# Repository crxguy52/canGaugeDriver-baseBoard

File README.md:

Hardware to to use [CANBed FD](https://www.seeedstudio.com/CANBed-FD-Arduino-CAN-FD-Development-Kit-p-4724.html) to read CAN data and drive gauges on a NB Miata

Used in conjunction with the [software](https://github.com/crxguy52/canGaugeDriver)

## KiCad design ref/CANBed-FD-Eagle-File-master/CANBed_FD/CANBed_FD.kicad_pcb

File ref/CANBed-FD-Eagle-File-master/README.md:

# CANBed-FD-Eagle-File
EAGLE FILE FOR CANBED-FD

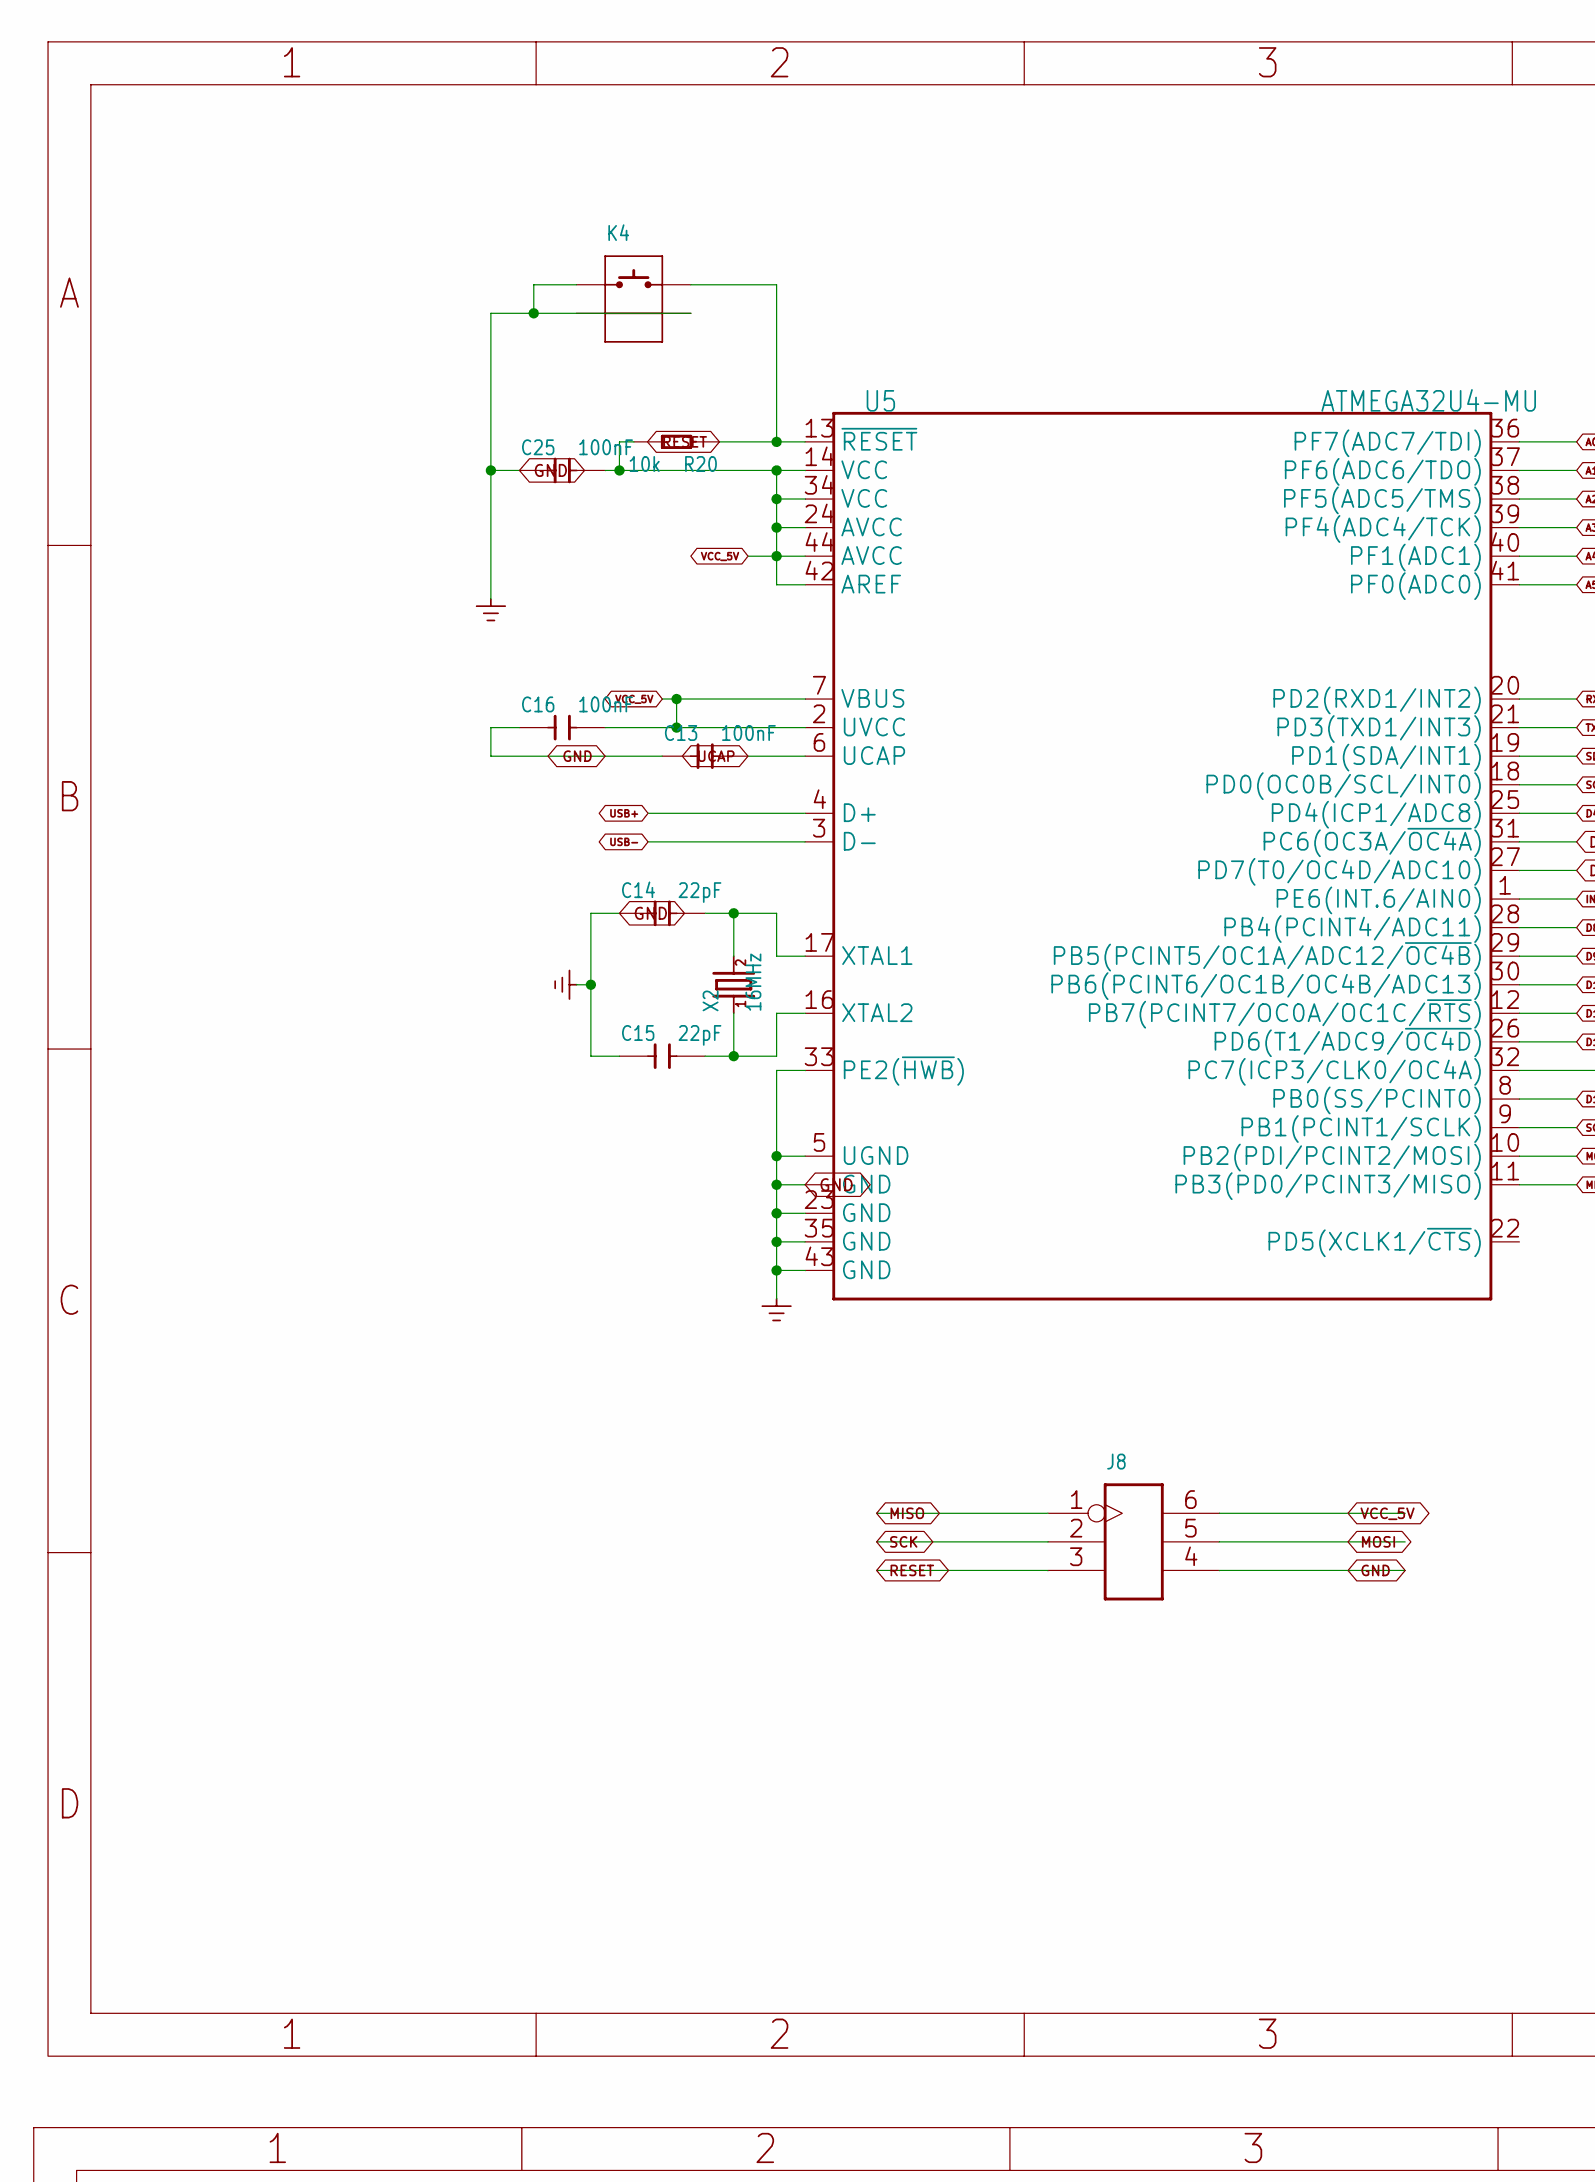
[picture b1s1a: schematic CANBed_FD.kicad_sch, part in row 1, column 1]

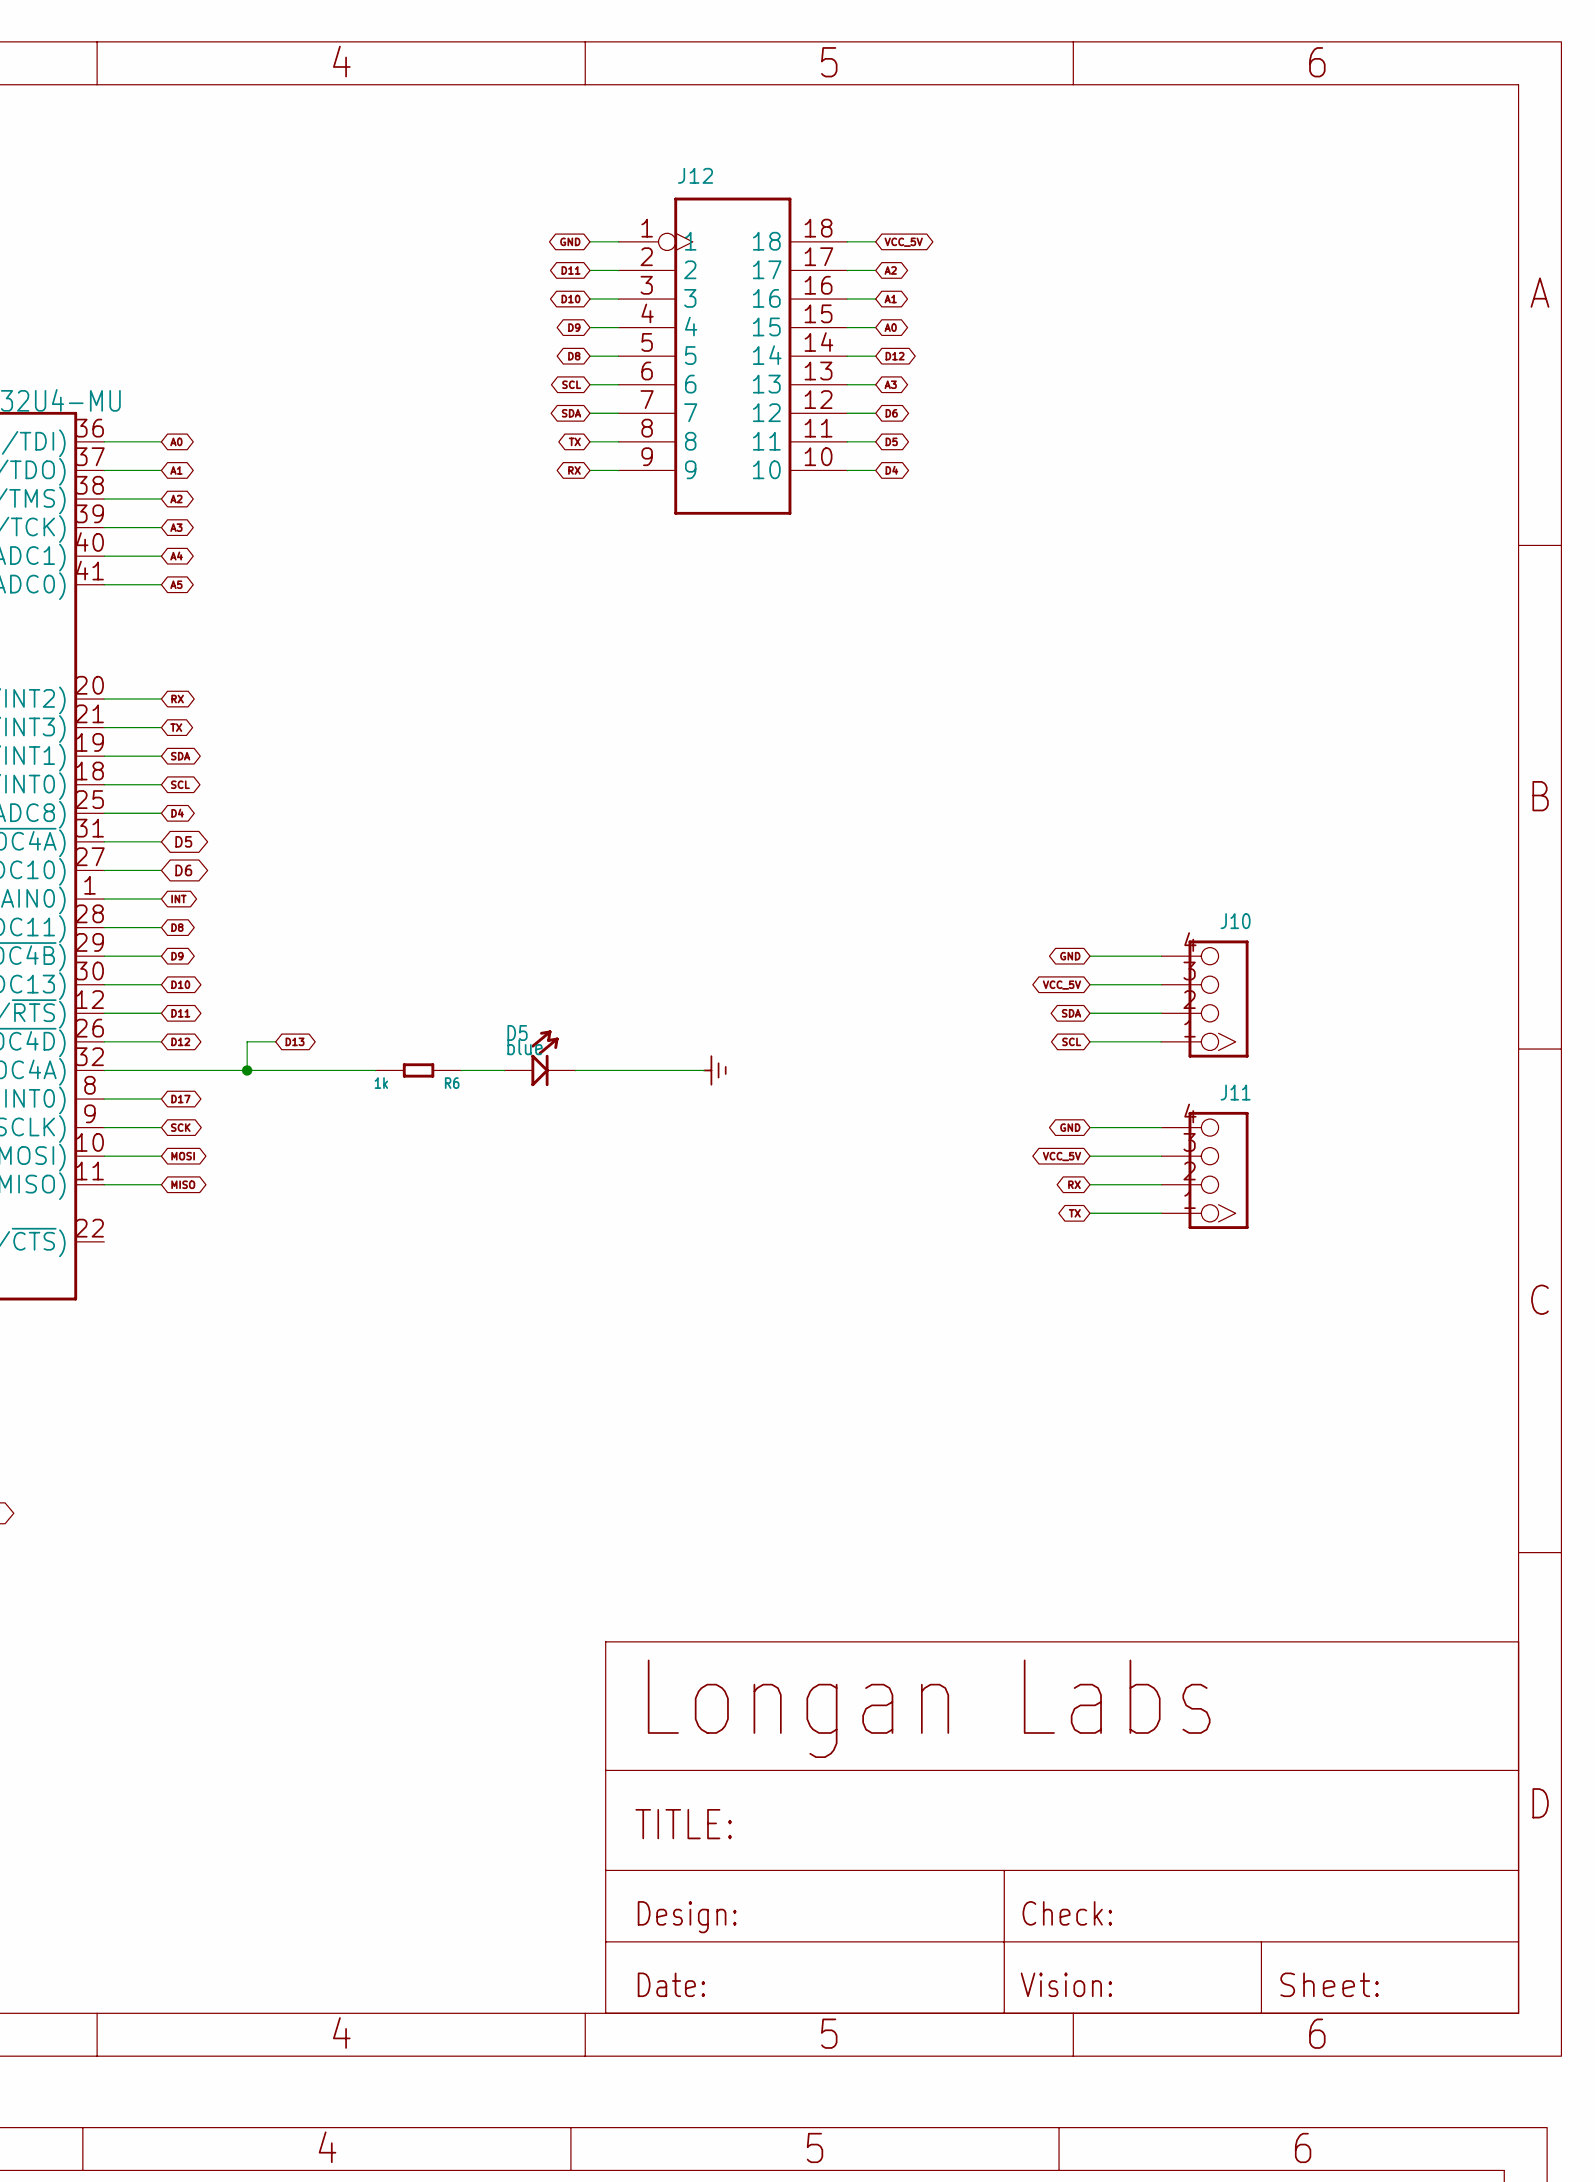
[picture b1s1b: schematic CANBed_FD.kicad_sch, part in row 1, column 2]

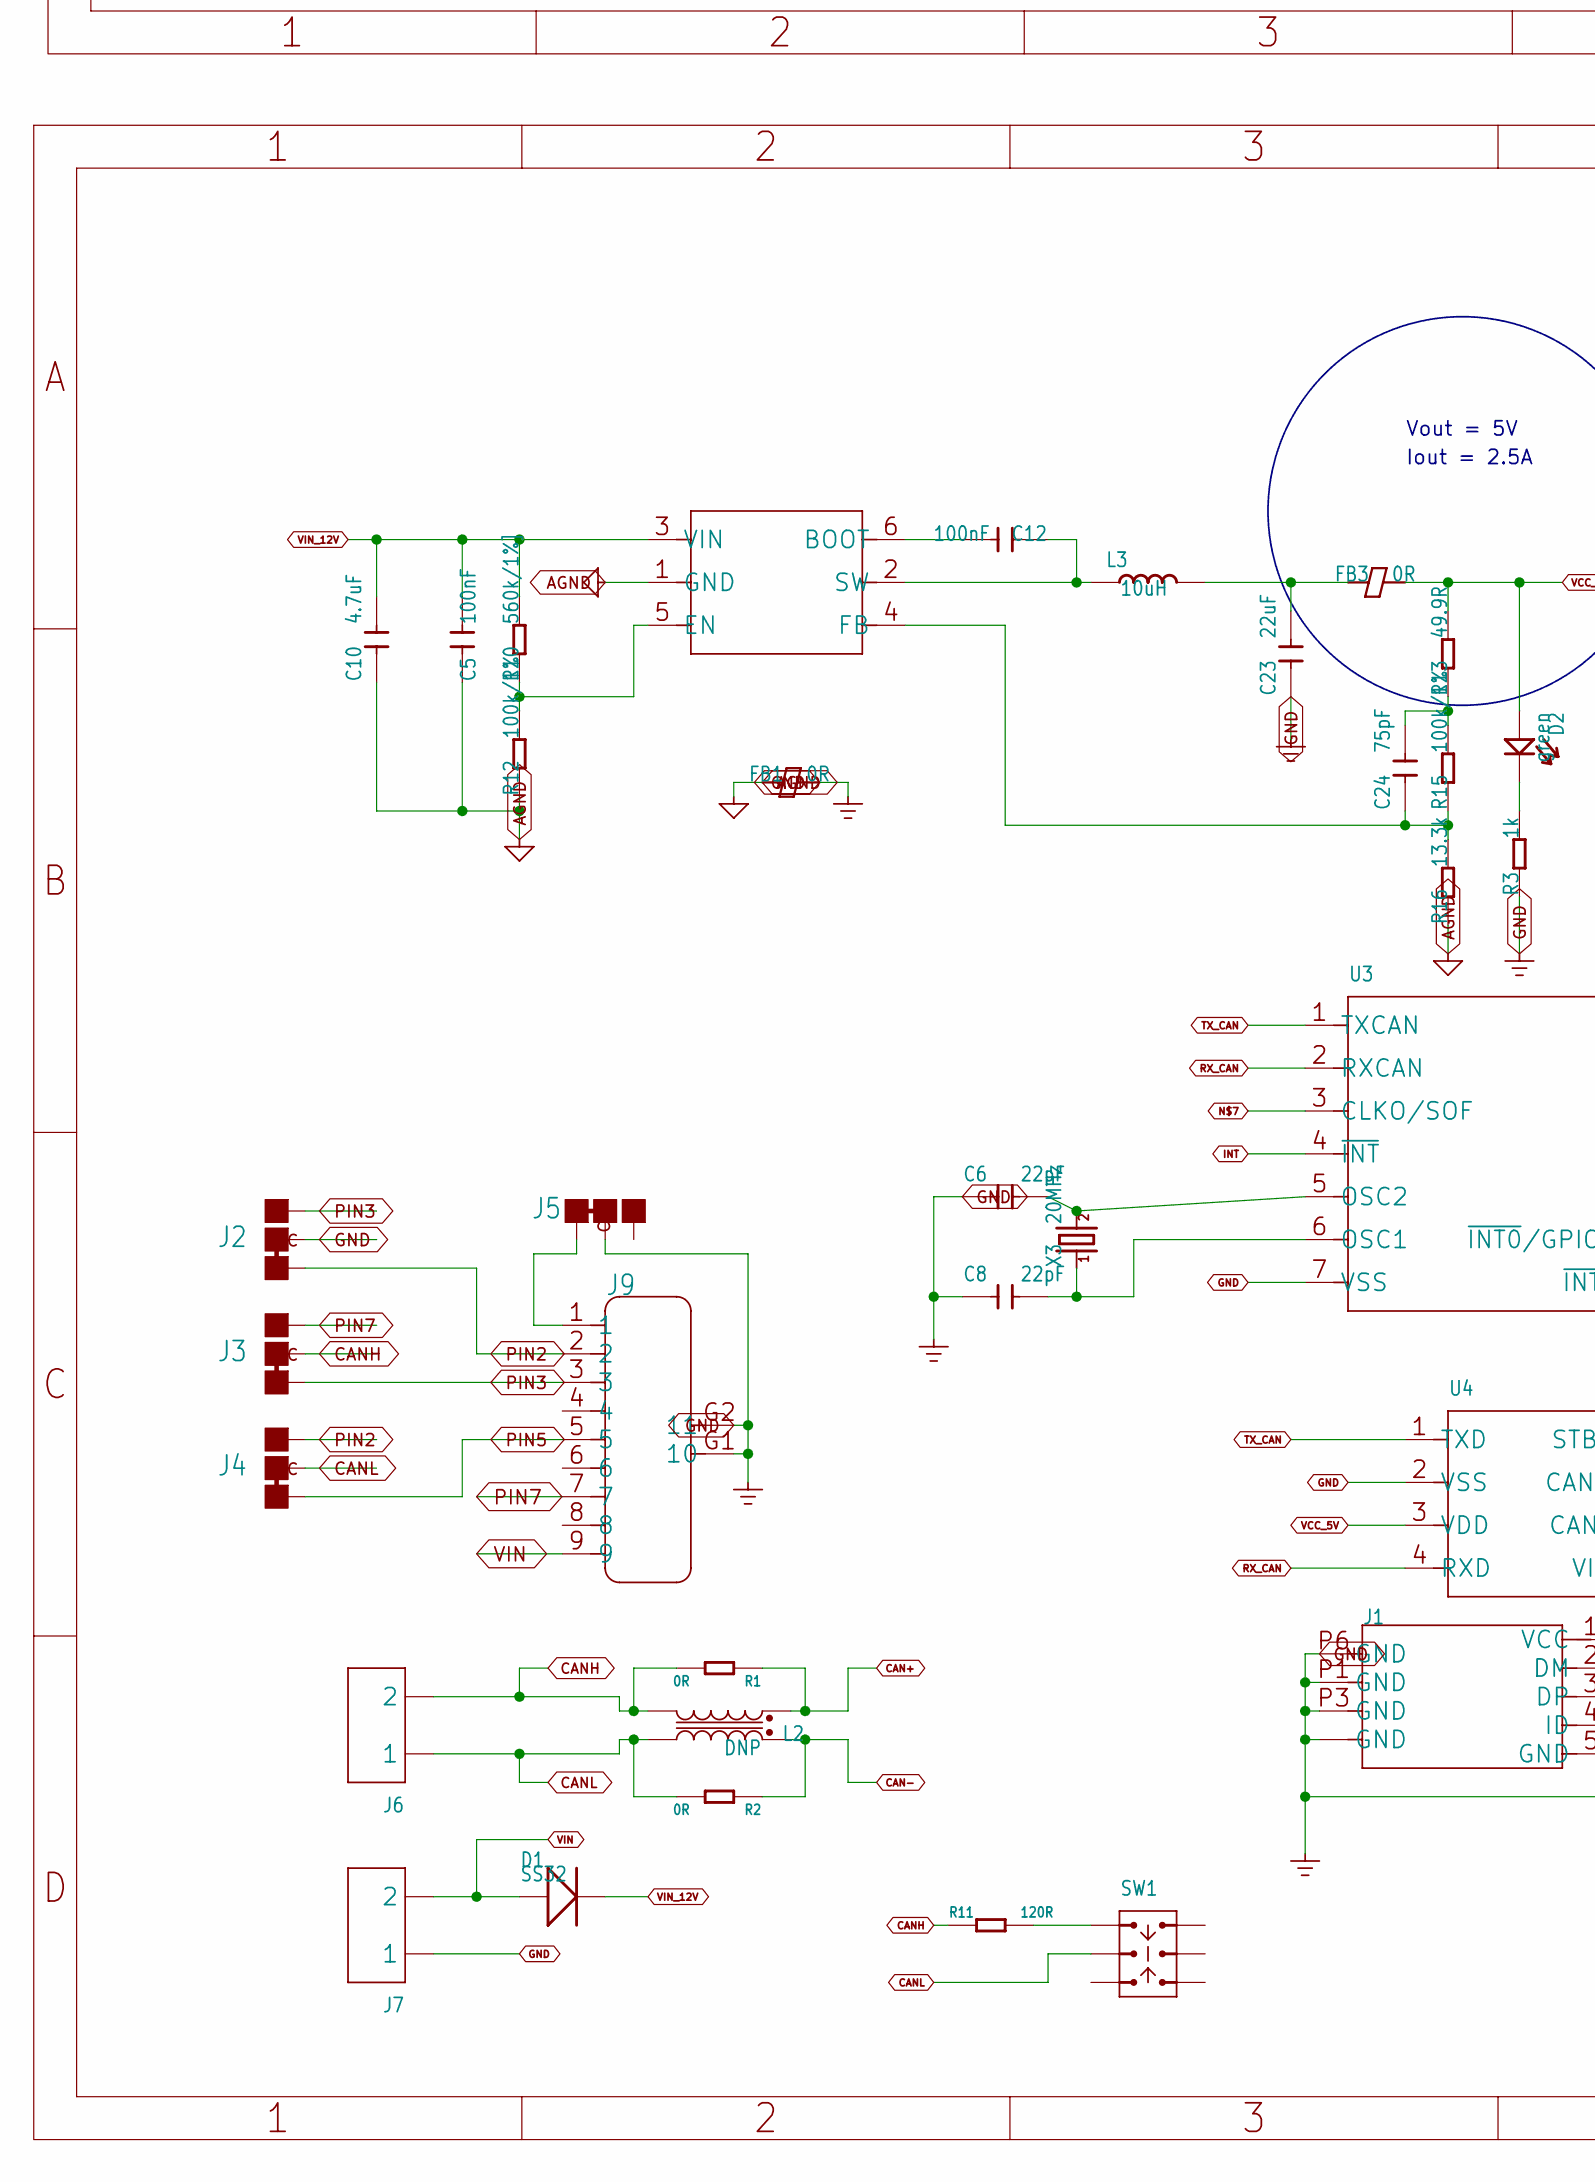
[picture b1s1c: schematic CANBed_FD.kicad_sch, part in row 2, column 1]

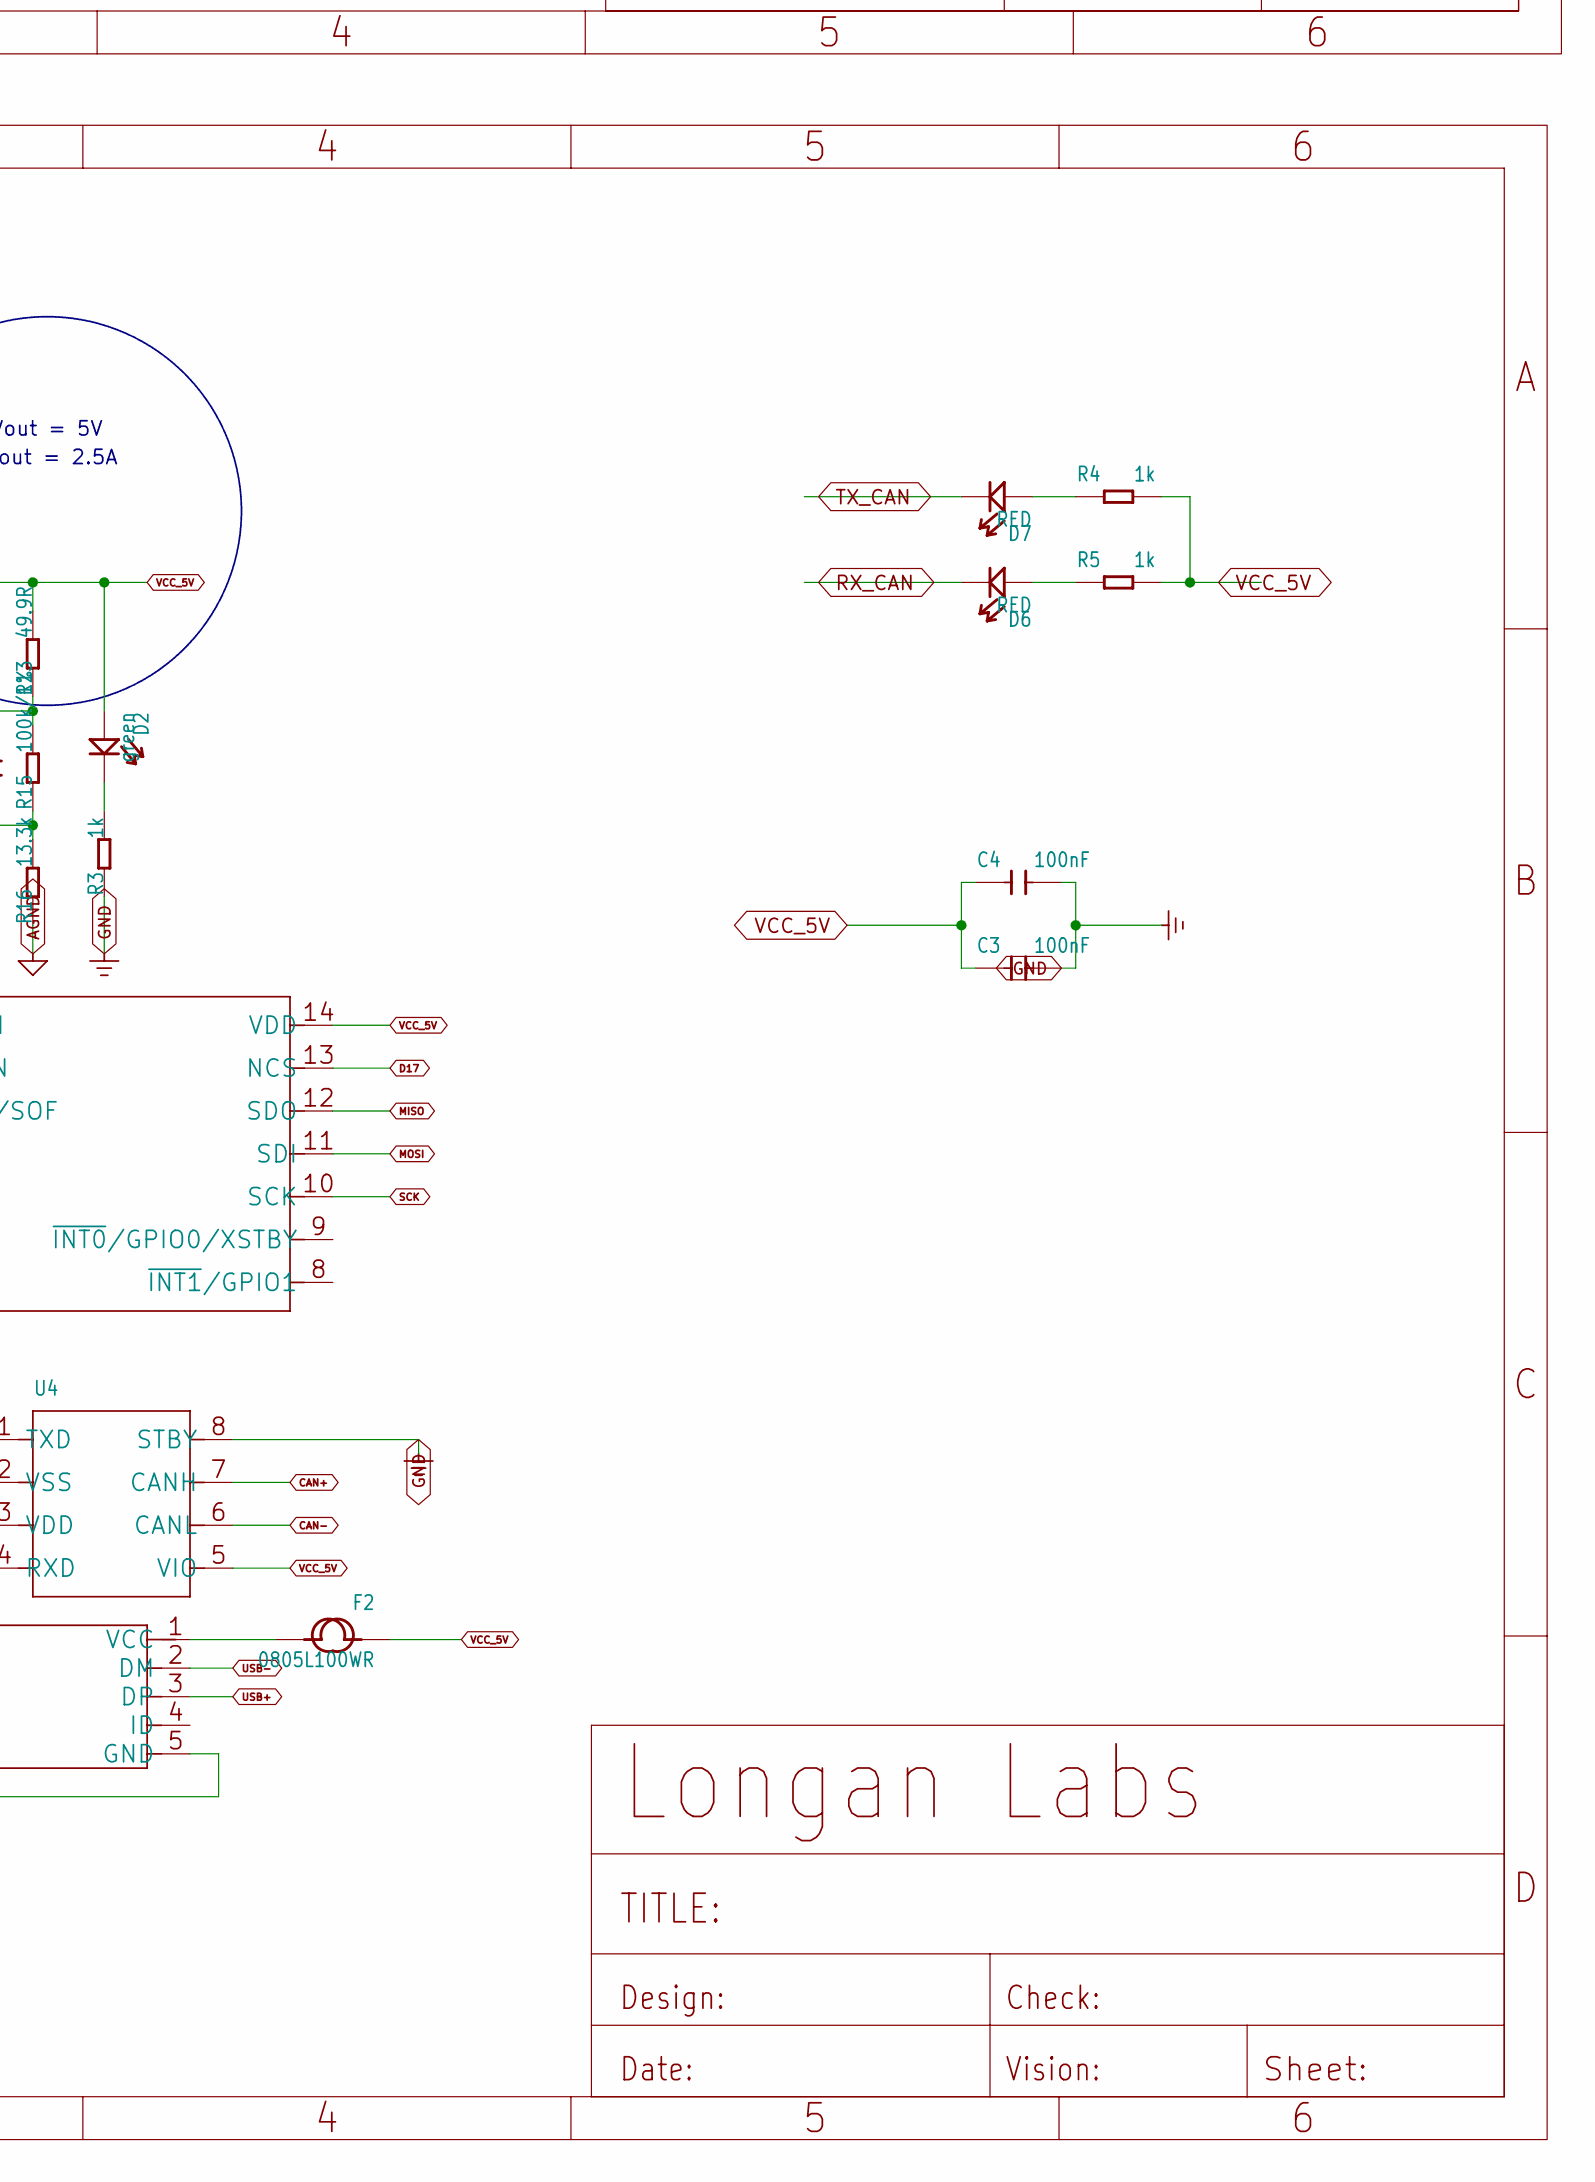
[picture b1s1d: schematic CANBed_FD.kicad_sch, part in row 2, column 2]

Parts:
C3, C4, C5, C12, C13, C16, C25: 100nF; C0603
C6, C8, C14, C15: 22pF; C0603
C10: 4.7uF; C1206
C23: 22uF; C1206
C24: 75pF; C0603
D1: SS32; DO-214AC
D2: green; LED-0603
D5: blue; LED-0603
D6, D7: RED; LED-0603
F2: 0805L100WR; F0805
FB1, FB3: 0R; F0805
J1: MICRO-USB5+4P-320010050; MICRO-USB5+5P-SMD-0.65-7.2X5.06MM
J2, J3, J4, J5: JUMPER-3P-SHORT; 3P-SMD-SHORT
J6, J7: SCREW-TERMINAL-2P'5.08'; H2-5.0-10.5X8.0MM
J8: HEADER-2X3P-2.54; H2X3-2.54
J9: DB9'MEAL'; DB9-MEAL
J10, J11: 320110033; HW4-2.0
J12: HEADER-2X9P-2.54; H2X9-2.54
K4: BUTTON-2+2P; SW2+2P-7.7X2.75X3.95MM
L2: DNP; INT4-0.85-2X1.25X1.2MM
L3: 10uH; INT2-SMD-6.6X7.1X3MM
R1, R2: 0R; R0603
R3, R4, R5, R6: 1k; R0603
R10: 560k/1%]; R0603
R11: 120R; R0603
R12, R15: 100k/1%; R0603
R13: 49.9R; R0603
R16: 13.3k; R0603
R20: 10k; R0603
SW1: SWITCH-2CH-6P-311010004; SW6-2.54-9.0X3.5X3.2+2.0MM
U3: CONTROLLER-MCP2517FD; SOIC14-1.27-8.6X3.9MM
U4: TRANSCEIVER-MCP2542; SOIC8-1.27-5X4MM
U5: ATMEGA32U4-MU; QFN44
U$11: PMIC-TPS54302; SOT-23-6
X2: 16MHz; HC49US
X3: 20MHz; HC49US

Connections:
A0: J12.15, U5.36 (PF7(ADC7/TDI))
A1: J12.16, U5.37 (PF6(ADC6/TDO))
A2: J12.17, U5.38 (PF5(ADC5/TMS))
A3: J12.13, U5.39 (PF4(ADC4/TCK))
A4: U5.40 (PF1(ADC1))
A5: U5.41 (PF0(ADC0))
AGND: C5.1, C10.1, FB1.1, R12.1, R16.1, U$11.1 (GND)
CAN+: L2.4, R1.1, U4.7 (CANH)
CAN-: L2.1, R2.1, U4.6 (CANL)
CANH: J3.MM (C), J6.2, L2.3, R1.2, R11.1
CANL: J4.MM (C), J6.1, L2.2, R2.2, SW1.COM1
D4: J12.10, U5.25 (PD4(ICP1/ADC8))
D5: J12.11, U5.31 (PC6(OC3A/~OC4A))
D6: J12.12, U5.27 (PD7(T0/OC4D/ADC10))
D8: J12.5, U5.28 (PB4(PCINT4/ADC11))
D9: J12.4, U5.29 (PB5(PCINT5/OC1A/ADC12/~OC4B))
D10: J12.3, U5.30 (PB6(PCINT6/OC1B/OC4B/ADC13))
D11: J12.2, U5.12 (PB7(PCINT7/OC0A/OC1C/~RTS))
D12: J12.14, U5.26 (PD6(T1/ADC9/~OC4D))
D13: R6.2, U5.32 (PC7(ICP3/CLK0/OC4A))
D17: U3.13 (NCS), U5.8 (PB0(SS/PCINT0))
EXT_PWR: F2.2, J1.1 (VCC)
GND: C3.2, C4.2, C6.1, C8.1, C13.1, C14.1, C15.1, C16.1, C23.1, C25.1, D5.-, FB1.2, J1.5 (GND), J1.P1 (GND), J1.P3 (GND), J1.P4 (GND), J1.P5 (GND), J1.P6 (GND), J2.MM (C), J5.MM (C), J7.1, J8.4, J9.G1 (10), J9.G2 (11), J10.4, J11.4, J12.1, K4.1, K4.S1, K4.S2, R3.1, U3.7 (VSS), U4.2 (VSS), U4.8 (STBY), U5.5 (UGND), U5.15 (GND), U5.23 (GND), U5.33 (PE2(~HWB)), U5.35 (GND), U5.43 (GND), U5.TAB (GND)
INT: U3.4 (~INT), U5.1 (PE6(INT.6/AIN0))
MISO: J8.1, U3.12 (SDO), U5.11 (PB3(PD0/PCINT3/MISO))
MOSI: J8.5, U3.11 (SDI), U5.10 (PB2(PDI/PCINT2/MOSI))
unnamed: D2.-, R3.2
unnamed: D7.+, R4.1
unnamed: R10.1, R12.2, U$11.5 (EN)
unnamed: C14.2, U5.17 (XTAL1), X2.2
unnamed: D5.+, R6.1
unnamed: C6.2, U3.5 (OSC2), X3.2
unnamed: C12.1, L3.1, U$11.2 (SW)
unnamed: C15.2, U5.16 (XTAL2), X2.1
unnamed: J5.11 (L), J9.1
unnamed: C12.2, U$11.6 (BOOT)
unnamed: D6.+, R5.1
unnamed: R11.2, SW1.CH1A
unnamed: C8.2, U3.6 (OSC1), X3.1
unnamed: C23.2, FB3.1, L3.2
unnamed: C24.2, R13.1, R15.2
unnamed: C24.1, R15.1, R16.2, U$11.4 (FB)
PIN2: J2.11 (L), J4.00 (R), J9.2
PIN3: J2.00 (R), J3.11 (L), J9.3
PIN5: J4.11 (L), J9.5
PIN7: J3.00 (R), J9.7
RESET: J8.3, K4.2, R20.1, U5.13 (~RESET)
RX: J11.2, J12.9, U5.20 (PD2(RXD1/INT2))
RX_CAN: D6.-, U3.2 (RXCAN), U4.4 (RXD)
SCK: J8.2, U3.10 (SCK), U5.9 (PB1(PCINT1/SCLK))
SCL: J10.1, J12.6, U5.18 (PD0(OC0B/SCL/INT0))
SDA: J10.2, J12.7, U5.19 (PD1(SDA/INT1))
TX: J11.1, J12.8, U5.21 (PD3(TXD1/INT3))
TX_CAN: D7.-, U3.1 (TXCAN), U4.1 (TXD)
UCAP: C13.2, U5.6 (UCAP)
USB+: J1.3 (DP), U5.4 (D+)
USB-: J1.2 (DM), U5.3 (D-)
VCC_5V: C3.1, C4.1, C16.2, C25.2, D2.+, F2.1, FB3.2, J8.6, J10.3, J11.3, J12.18, R4.2, R5.2, R13.2, R20.2, U3.14 (VDD), U4.3 (VDD), U4.5 (VIO), U5.2 (UVCC), U5.7 (VBUS), U5.14 (VCC), U5.24 (AVCC), U5.34 (VCC), U5.42 (AREF), U5.44 (AVCC)
VIN: D1.1 (+), J7.2, J9.9
VIN_12V: C5.2, C10.2, D1.2 (-), R10.2, U$11.3 (VIN)

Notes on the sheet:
Iout = 2.5A
Vout = 5V

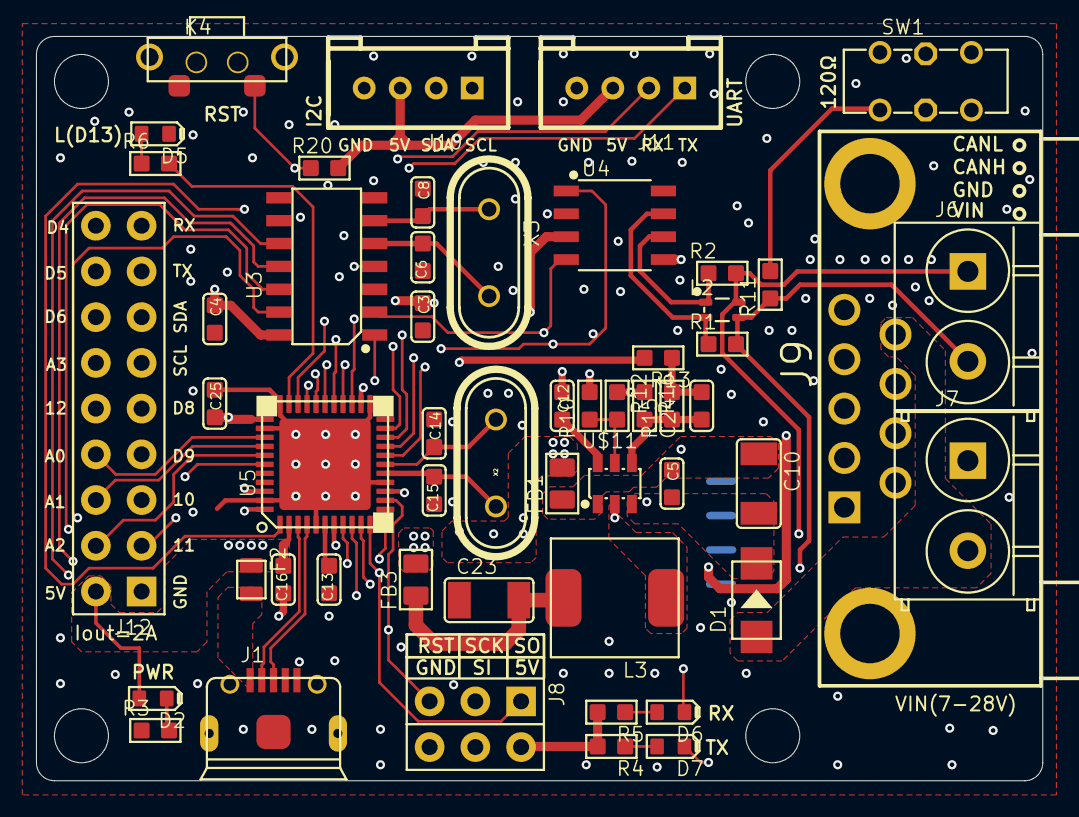
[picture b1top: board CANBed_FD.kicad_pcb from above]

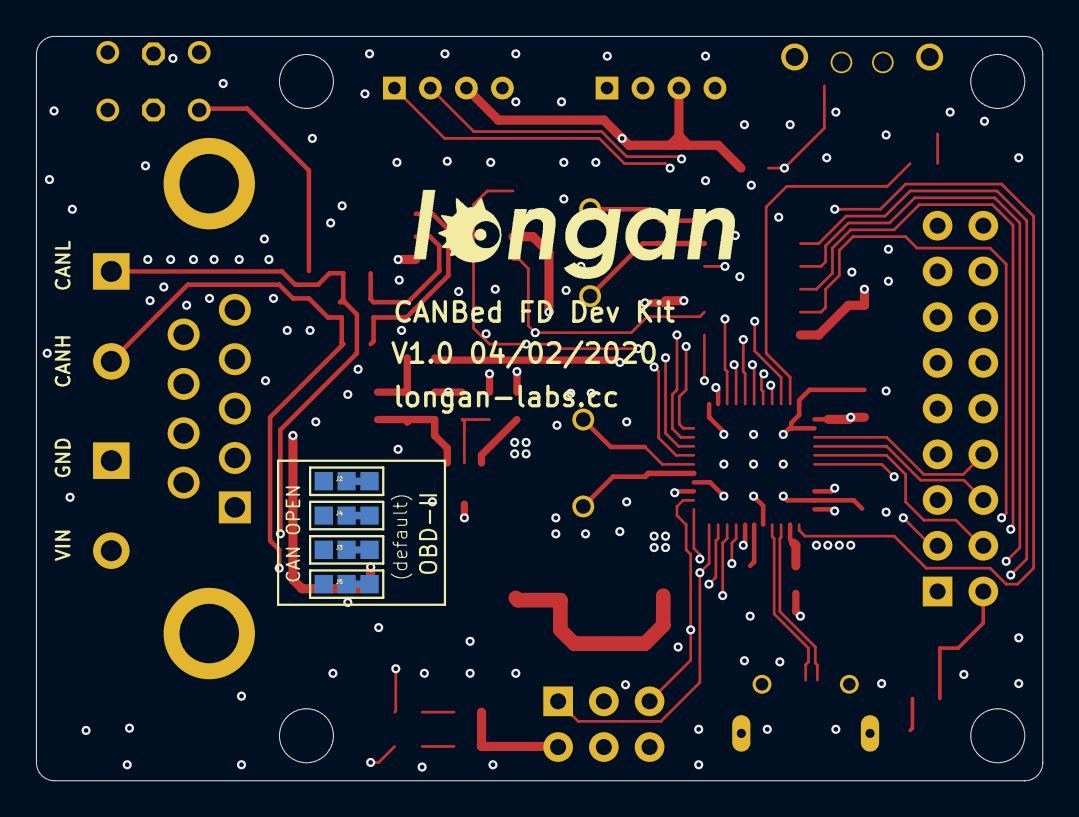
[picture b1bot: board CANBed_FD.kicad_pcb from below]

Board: 6 copper layers, 55.9 x 41.4 mm, 62 parts (5 on the bottom side), 58 nets.

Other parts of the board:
U$12: LONGAN-SILK-SMALL
UNK_HOLE_0: dummyfp0
UNK_HOLE_1: dummyfp1
UNK_HOLE_2: dummyfp2
UNK_HOLE_3: dummyfp3

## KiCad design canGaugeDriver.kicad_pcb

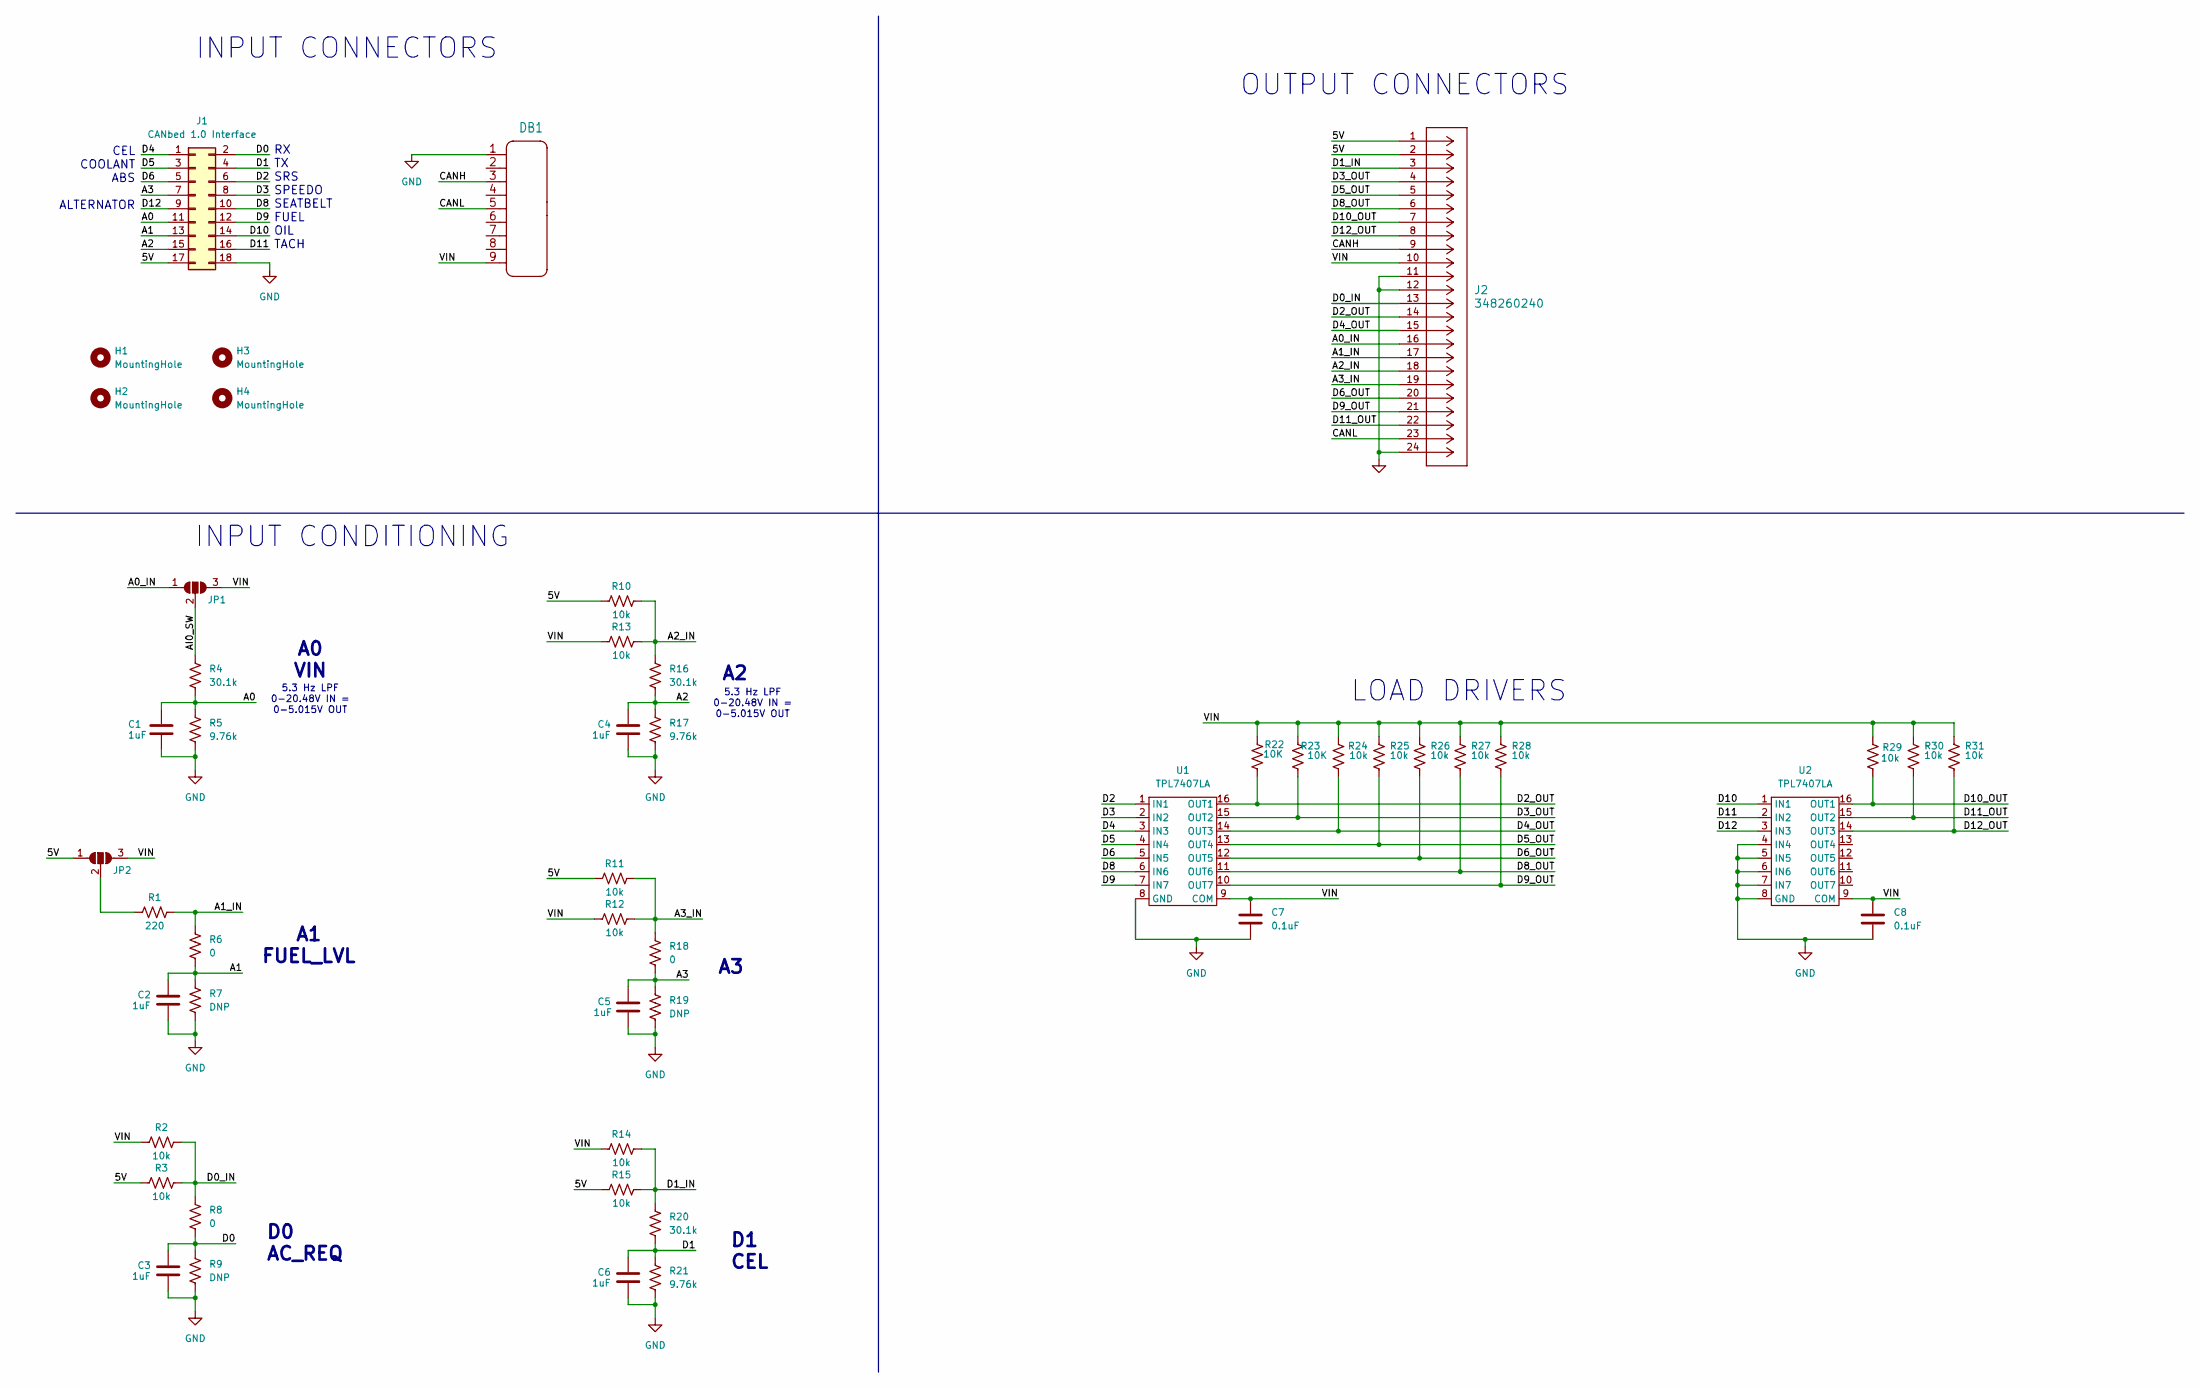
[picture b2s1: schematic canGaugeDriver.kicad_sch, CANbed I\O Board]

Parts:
C1, C2, C3, C4, C5, C6: 1uF; C_0805_2012Metric_Pad1.18x1.45mm_HandSolder
C7, C8: 0.1uF; C_0805_2012Metric_Pad1.18x1.45mm_HandSolder
DB1: DB9'MEAL'; DB9-MEAL
H1, H2, H3, H4: MountingHole; MountingHole_3mm
J1: CANbed 1.0 Interface; PinHeader_2x09_P2.54mm_Vertical
J2: 348260240; CONN_SD-34826-001_24_MOL
JP1, JP2: SolderJumper_3_Open; SolderJumper-3_P1.3mm_Open_Pad1.0x1.5mm_NumberLabels
R1: 220; R_2512_6332Metric
R2, R3, R10, R11, R12, R13, R14, R15, R24, R25, R26, R27, R28, R29, R30, R31: 10k; R_0805_2012Metric_Pad1.20x1.40mm_HandSolder
R4, R16, R20: 30.1k; R_0805_2012Metric_Pad1.20x1.40mm_HandSolder
R5, R17, R21: 9.76k; R_0805_2012Metric_Pad1.20x1.40mm_HandSolder
R6, R8, R18: 0; R_0805_2012Metric_Pad1.20x1.40mm_HandSolder
R7, R9, R19: DNP; R_0805_2012Metric_Pad1.20x1.40mm_HandSolder
R22, R23: 10K; R_0805_2012Metric_Pad1.20x1.40mm_HandSolder
U1, U2: TPL7407LA; SOIC-16_3.9x9.9mm_P1.27mm

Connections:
/5V: J1.17, J2.1, J2.2, JP2.1 (A), R3.2, R10.2, R11.2, R15.2
/A0: C1.1, J1.11, R4.2, R5.1
/A0_IN: J2.16, JP1.1 (A)
/A1: C2.1, J1.13, R6.2, R7.1
/A1_IN: J2.17, R1.1, R6.1
/A2: C4.1, J1.15, R16.2, R17.1
/A2_IN: J2.18, R10.1, R13.1, R16.1
/A3: C5.1, J1.7, R18.2, R19.1
/A3_IN: J2.19, R11.1, R12.1, R18.1
/AI0_SW: JP1.2 (C), R4.1
/CANH: DB1.3, J2.9
/CANL: DB1.5, J2.23
/D0: C3.1, J1.2, R8.2, R9.1
/D0_IN: J2.13, R2.1, R3.1, R8.1
/D1: C6.1, J1.4, R20.2, R21.1
/D1_IN: J2.3, R14.1, R15.1, R20.1
/D2: J1.6, U1.1 (IN1)
/D2_OUT: J2.14, R22.1, U1.16 (OUT1)
/D3: J1.8, U1.2 (IN2)
/D3_OUT: J2.4, R23.2, U1.15 (OUT2)
/D4: J1.1, U1.3 (IN3)
/D4_OUT: J2.15, R24.2, U1.14 (OUT3)
/D5: J1.3, U1.4 (IN4)
/D5_OUT: J2.5, R25.2, U1.13 (OUT4)
/D6: J1.5, U1.5 (IN5)
/D6_OUT: J2.20, R26.2, U1.12 (OUT5)
/D8: J1.10, U1.6 (IN6)
/D8_OUT: J2.6, R27.2, U1.11 (OUT6)
/D9: J1.12, U1.7 (IN7)
/D9_OUT: J2.21, R28.2, U1.10 (OUT7)
/D10: J1.14, U2.1 (IN1)
/D10_OUT: J2.7, R29.2, U2.16 (OUT1)
/D11: J1.16, U2.2 (IN2)
/D11_OUT: J2.22, R30.2, U2.15 (OUT2)
/D12: J1.9, U2.3 (IN3)
/D12_OUT: J2.8, R31.2, U2.14 (OUT3)
/VIN: C7.1, C8.1, DB1.9, J2.10, JP1.3 (B), JP2.3 (B), R2.2, R12.2, R13.2, R14.2, R22.2, R23.1, R24.1, R25.1, R26.1, R27.1, R28.1, R29.1, R30.1, R31.1, U1.9 (COM), U2.9 (COM)
GND: C1.2, C2.2, C3.2, C4.2, C5.2, C6.2, C7.2, C8.2, DB1.1, J1.18, J2.11, J2.12, J2.24, R5.2, R7.2, R9.2, R17.2, R19.2, R21.2, U1.8 (GND), U2.4 (IN4), U2.5 (IN5), U2.6 (IN6), U2.7 (IN7), U2.8 (GND)
unnamed: JP2.2 (C), R1.2

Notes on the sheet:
D0 AC_REQ
5.3 Hz LPF 0-20.48V IN = 0-5.015V OUT
INPUT CONNECTORS
INPUT CONDITIONING
RX TX SRS SPEEDO SEATBELT FUEL OIL TACH
A0 VIN
LOAD DRIVERS
D1 CEL
OUTPUT CONNECTORS
CEL COOLANT ABS ALTERNATOR
A1 FUEL_LVL
